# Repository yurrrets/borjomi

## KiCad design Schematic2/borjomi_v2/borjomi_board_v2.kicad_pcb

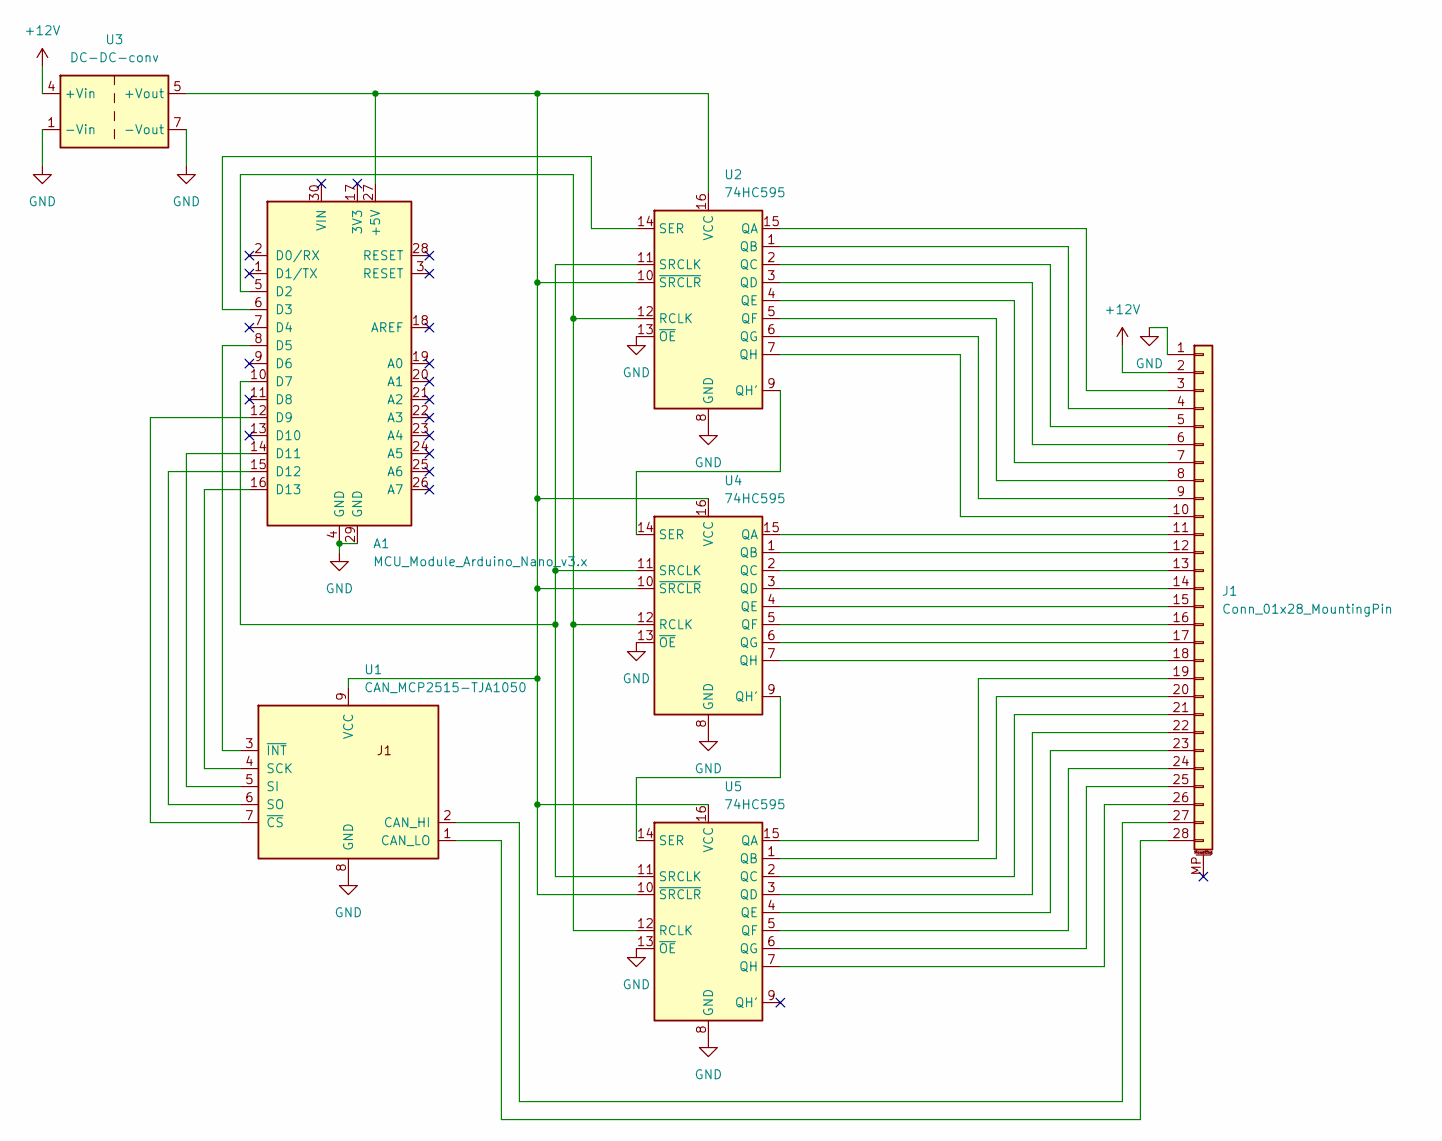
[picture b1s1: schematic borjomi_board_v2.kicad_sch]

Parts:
A1: MCU_Module_Arduino_Nano_v3.x; Arduino_Nano_Holes0.9
J1: Conn_01x28_MountingPin; PinHeader_1x28_P2.54mm_Vertical
U1: CAN_MCP2515-TJA1050; AOC346_MCP2515_Holes0.9
U2, U4, U5: 74HC595; DIP-16_W7.62mm
U3: DC-DC-conv; DC_DC_Step_Out

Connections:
+12V: J1.2, U3.4 (+Vin)
GND: A1.4 (GND), A1.29 (GND), J1.1, U1.8 (GND), U2.8 (GND), U2.13 (~OE), U3.1 (-Vin), U3.7 (-Vout), U4.8 (GND), U4.13 (~OE), U5.8 (GND), U5.13 (~OE)
unnamed: A1.27 (+5V), U1.9 (VCC), U2.10 (~SRCLR), U2.16 (VCC), U3.5 (+Vout), U4.10 (~SRCLR), U4.16 (VCC), U5.10 (~SRCLR), U5.16 (VCC)
unnamed: A1.5 (D2), U2.12 (RCLK), U4.12 (RCLK), U5.12 (RCLK)
unnamed: A1.6 (D3), U2.14 (SER)
unnamed: A1.8 (D5), U1.3 (~INT)
unnamed: A1.10 (D7), U2.11 (SRCLK), U4.11 (SRCLK), U5.11 (SRCLK)
unnamed: A1.12 (D9), U1.7 (~CS)
unnamed: A1.14 (D11), U1.5 (SI)
unnamed: A1.15 (D12), U1.6 (SO)
unnamed: A1.16 (D13), U1.4 (SCK)
unnamed: J1.3, U2.15 (QA)
unnamed: J1.4, U2.1 (QB)
unnamed: J1.5, U2.2 (QC)
unnamed: J1.6, U2.3 (QD)
unnamed: J1.7, U2.4 (QE)
unnamed: J1.8, U2.5 (QF)
unnamed: J1.9, U2.6 (QG)
unnamed: J1.10, U2.7 (QH)
unnamed: J1.11, U4.15 (QA)
unnamed: J1.12, U4.1 (QB)
unnamed: J1.13, U4.2 (QC)
unnamed: J1.14, U4.3 (QD)
unnamed: J1.15, U4.4 (QE)
unnamed: J1.16, U4.5 (QF)
unnamed: J1.17, U4.6 (QG)
unnamed: J1.18, U4.7 (QH)
unnamed: J1.19, U5.15 (QA)
unnamed: J1.20, U5.1 (QB)
unnamed: J1.21, U5.2 (QC)
unnamed: J1.22, U5.3 (QD)
unnamed: J1.23, U5.4 (QE)
unnamed: J1.24, U5.5 (QF)
unnamed: J1.25, U5.6 (QG)
unnamed: J1.26, U5.7 (QH)
unnamed: J1.27, U1.2 (CAN_HI)
unnamed: J1.28, U1.1 (CAN_LO)
unnamed: U2.9 (QH'), U4.14 (SER)
unnamed: U4.9 (QH'), U5.14 (SER)

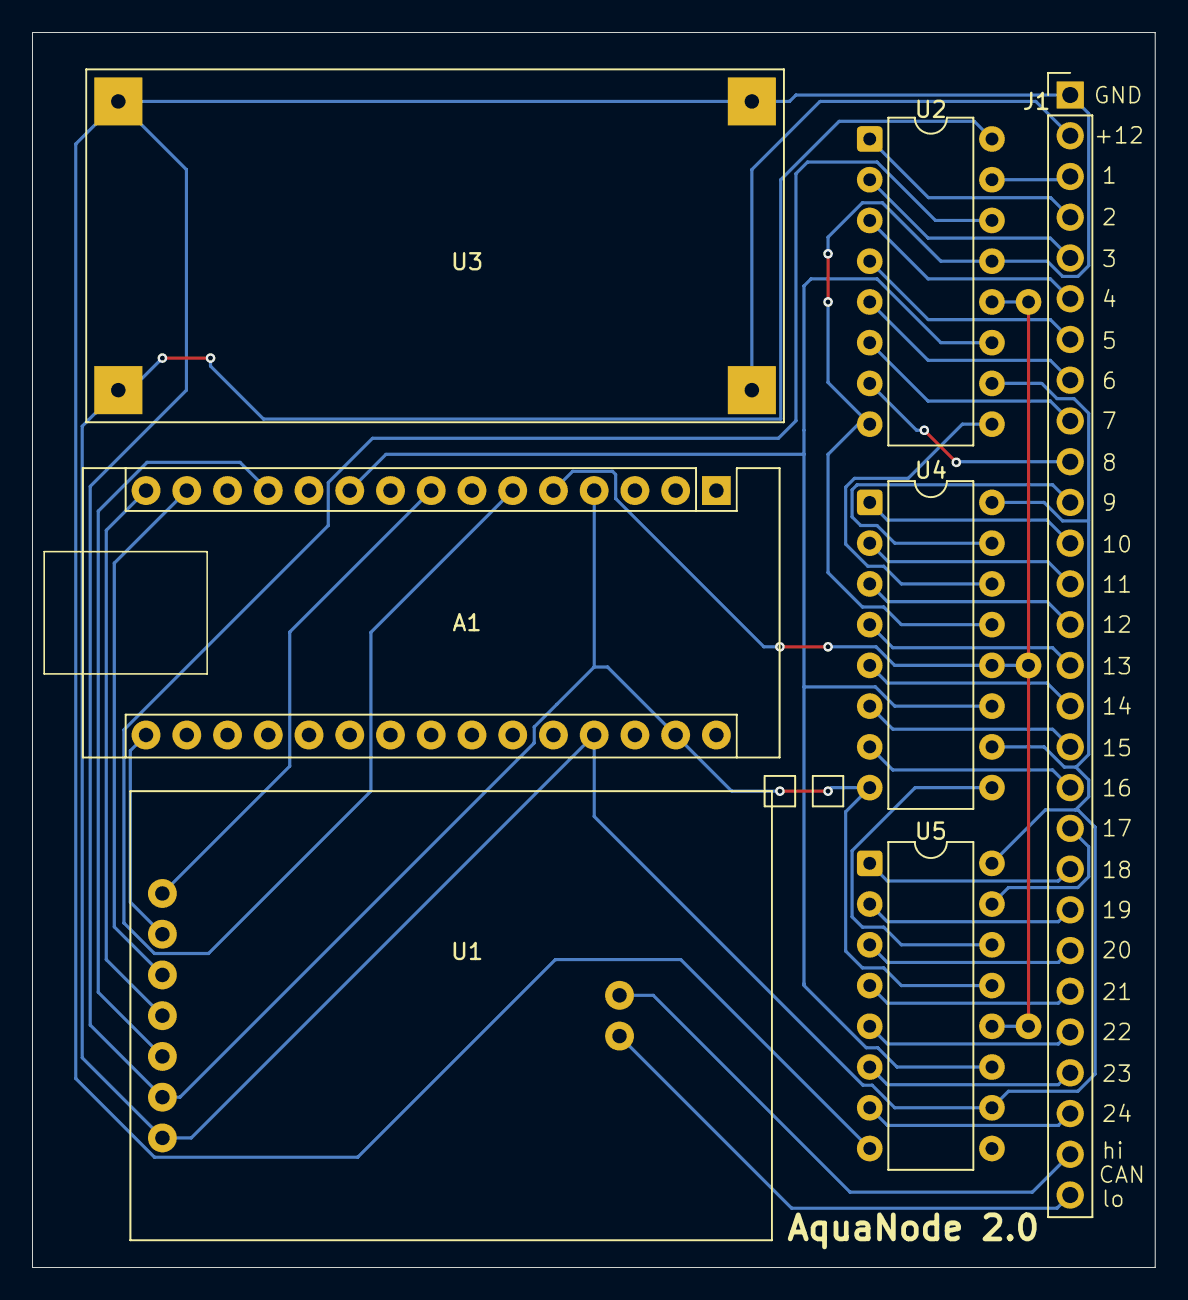
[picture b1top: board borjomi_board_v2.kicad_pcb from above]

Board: 2 copper layers, 70.0 x 77.0 mm, 7 parts (0 on the bottom side), 39 nets.

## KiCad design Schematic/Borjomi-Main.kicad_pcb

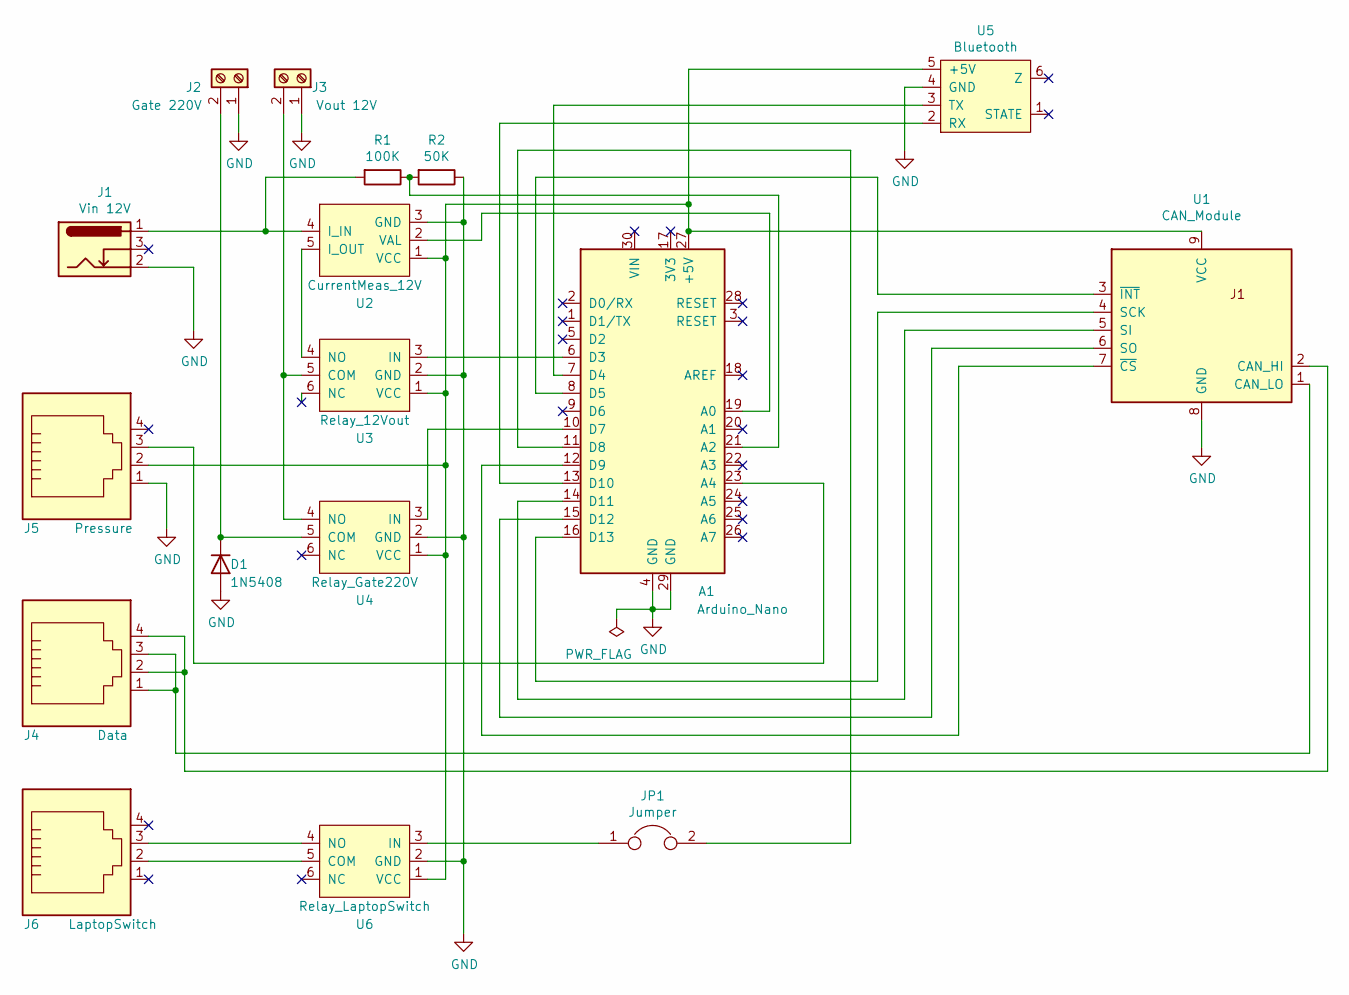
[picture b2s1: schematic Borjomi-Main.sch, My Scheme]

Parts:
A1: Arduino_Nano; Arduino_Nano_Holes0.9
D1: 1N5408; D_DO-27_P5.08mm_Vertical_KathodeUp
J1: Vin 12V; BarrelJack_Horizontal
J2: Gate 220V; Degson_DG301_1x02_P5.00mm_Horizontal
J3: Vout 12V; Degson_DG301_1x02_P5.00mm_Horizontal
J4: Data; RJ14_YH-57-21_5722_6P4C
J5: Pressure; RJ14_YH-57-21_5722_6P4C
J6: LaptopSwitch; RJ14_YH-57-21_5722_6P4C
JP1: Jumper; SimpleJumper_Pitch5.08mm_Drill0.7mm_2pad
R1: 100K; R_Box_L8.4mm_W2.5mm_P5.08mm
R2: 50K; R_Box_L8.4mm_W2.5mm_P5.08mm
U1: CAN_Module; AOC346_MCP2515_Holes0.9
U2: CurrentMeas_12V; ACS712
U3: Relay_12Vout; Relay_Module_1_Channel_Holes0.9
U4: Relay_Gate220V; Relay_Module_1_Channel_Holes0.9
U5: Bluetooth; HC-05
U6: Relay_LaptopSwitch; Relay_Module_1_Channel_Holes0.9

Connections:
GND: A1.4 (GND), A1.29 (GND), D1.2 (A), J1.2, J2.1, J3.1, J5.1, R2.1, U1.8 (GND), U2.3 (GND), U3.2 (GND), U4.2 (GND), U5.4 (GND), U6.2 (GND)
unnamed: A1.6 (D3), U3.3 (IN)
unnamed: A1.7 (D4), U5.3 (TX)
unnamed: A1.8 (D5), U1.3 (~INT)
unnamed: A1.10 (D7), U4.3 (IN)
unnamed: A1.11 (D8), JP1.2
unnamed: A1.12 (D9), U1.7 (~CS)
unnamed: A1.13 (D10), U5.2 (RX)
unnamed: A1.14 (D11), U1.5 (SI)
unnamed: A1.15 (D12), U1.6 (SO)
unnamed: A1.16 (D13), U1.4 (SCK)
unnamed: A1.19 (A0), U2.2 (VAL)
unnamed: A1.21 (A2), R1.1, R2.2
unnamed: A1.23 (A4), J5.3
unnamed: A1.27 (+5V), J5.2, U1.9 (VCC), U2.1 (VCC), U3.1 (VCC), U4.1 (VCC), U5.5 (+5V), U6.1 (VCC)
unnamed: D1.1 (K), J2.2, U4.5 (COM)
unnamed: J1.1, R1.2, U2.4 (I_IN)
unnamed: J3.2, U3.5 (COM), U4.4 (NO)
unnamed: J4.1, J4.3, U1.1 (CAN_LO)
unnamed: J4.2, J4.4, U1.2 (CAN_HI)
unnamed: J6.2, U6.5 (COM)
unnamed: J6.3, U6.4 (NO)
unnamed: JP1.1, U6.3 (IN)
unnamed: U2.5 (I_OUT), U3.4 (NO)

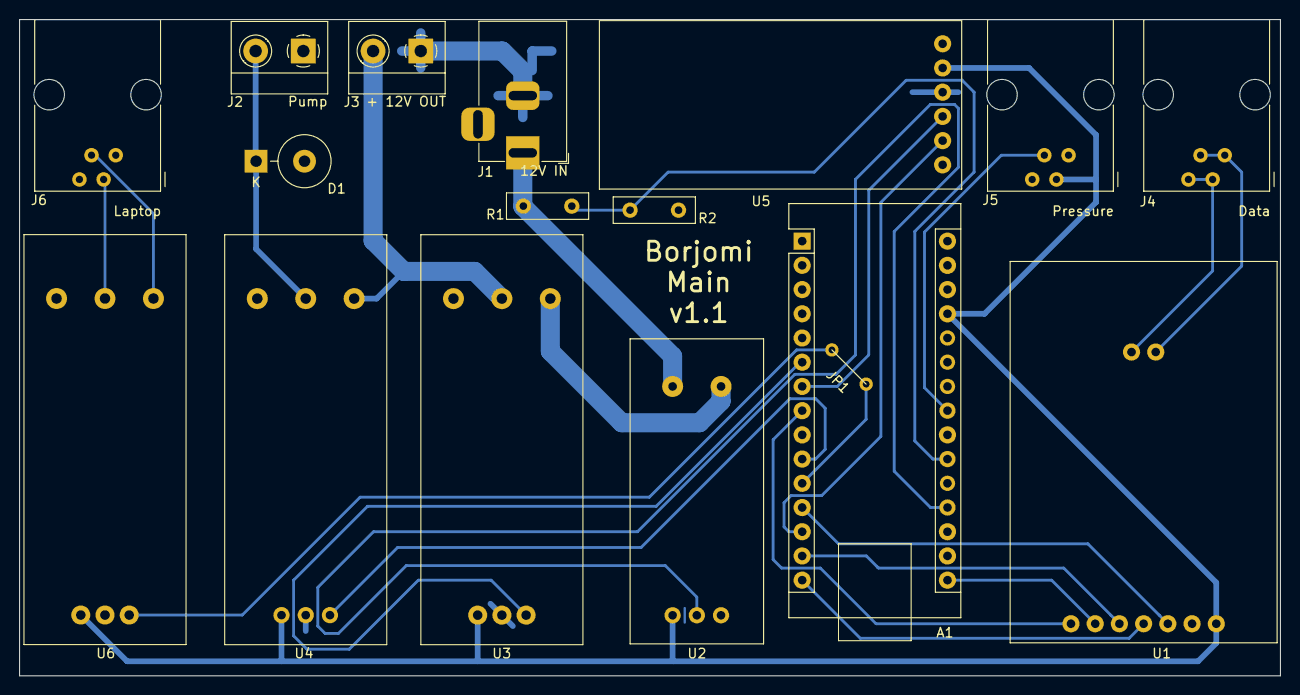
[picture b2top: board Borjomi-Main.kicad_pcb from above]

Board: 2 copper layers, 132.3 x 68.8 mm, 17 parts (0 on the bottom side), 24 nets.

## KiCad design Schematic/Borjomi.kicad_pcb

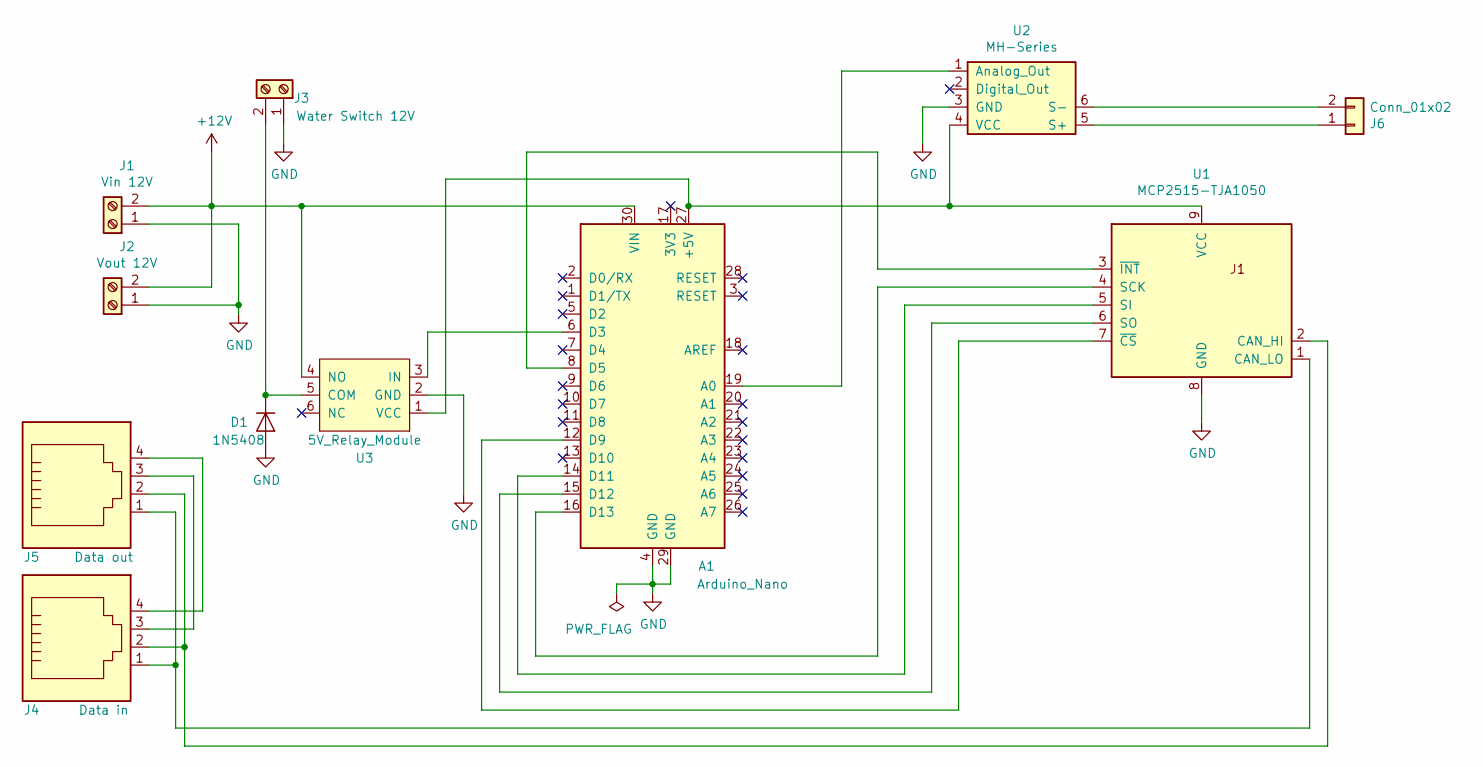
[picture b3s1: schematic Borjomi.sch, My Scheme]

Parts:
A1: Arduino_Nano; Arduino_Nano_Holes0.9
D1: 1N5408; D_DO-27_P5.08mm_Vertical_KathodeUp
J1: Vin 12V; Degson_DG301_1x02_P5.00mm_Horizontal
J2: Vout 12V; Degson_DG301_1x02_P5.00mm_Horizontal
J3: Water Switch 12V; Degson_DG301_1x02_P5.00mm_Horizontal
J4: Data in; RJ14_YH-57-21_5722_6P4C
J5: Data out; RJ14_YH-57-21_5722_6P4C
J6: Conn_01x02; Degson_DG301_1x02_P5.00mm_Horizontal
U1: MCP2515-TJA1050; AOC346_MCP2515_Holes0.9
U2: MH-Series; MH_Sensor_Holes0.9
U3: 5V_Relay_Module; Relay_Module_1_Channel_Holes0.9

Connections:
+12V: A1.30 (VIN), J1.2, J2.2, U3.4 (NO)
GND: A1.4 (GND), A1.29 (GND), D1.2 (A), J1.1, J2.1, J3.1, U1.8 (GND), U2.3 (GND), U3.2 (GND)
unnamed: A1.6 (D3), U3.3 (IN)
unnamed: A1.8 (D5), U1.3 (~INT)
unnamed: A1.12 (D9), U1.7 (~CS)
unnamed: A1.14 (D11), U1.5 (SI)
unnamed: A1.15 (D12), U1.6 (SO)
unnamed: A1.16 (D13), U1.4 (SCK)
unnamed: A1.19 (A0), U2.1 (Analog_Out)
unnamed: A1.27 (+5V), U1.9 (VCC), U2.4 (VCC), U3.1 (VCC)
unnamed: D1.1 (K), J3.2, U3.5 (COM)
unnamed: J4.1, J5.1, U1.1 (CAN_LO)
unnamed: J4.2, J5.2, U1.2 (CAN_HI)
unnamed: J4.3, J5.3
unnamed: J4.4, J5.4
unnamed: J6.1, U2.5 (S+)
unnamed: J6.2, U2.6 (S-)

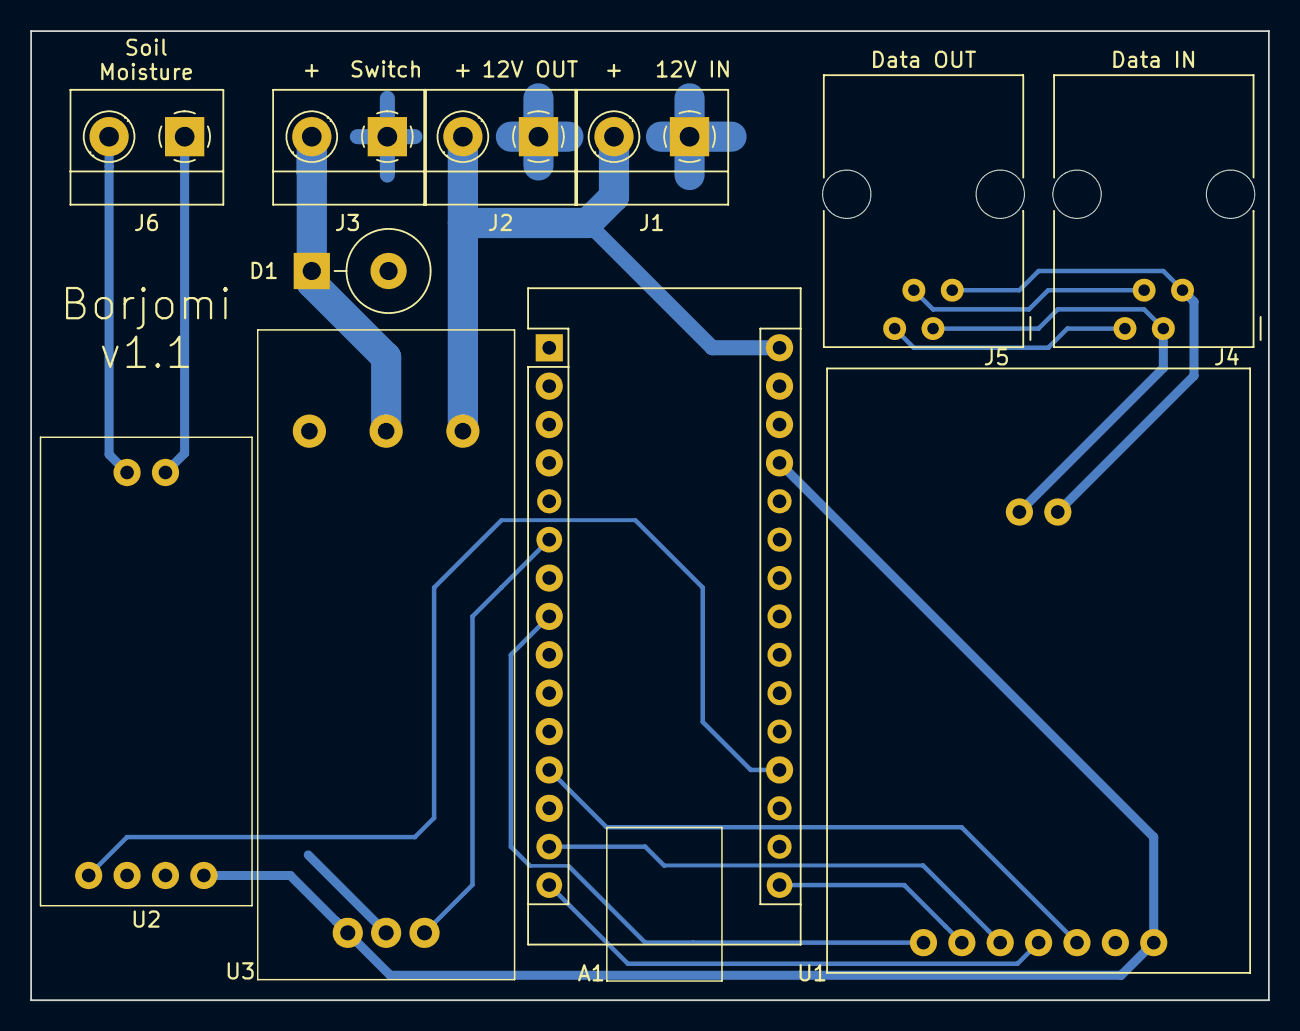
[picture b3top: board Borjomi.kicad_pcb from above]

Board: 2 copper layers, 81.9 x 64.1 mm, 11 parts (0 on the bottom side), 17 nets.

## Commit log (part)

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2018-09-18 add Arduino folder
2018-09-24 Add Creator files for common node
2018-09-27 Add Bluetooth protocol (draft), and first code to work with BT
2018-09-28 Add bluetooth support for water on/off command
2018-09-29 Reorganize code in master node
    Also recompile slave nodes for new EEPROM library
2018-09-29 Implement CMD_GET_WATER_SWITCH, plus code reorganization
2018-09-29 Improve CMD_GET_WATER_SWITCH answer
2018-09-30 Implement protocol on slave node side. Plus
    implement ANALOG_READ on higher level
2018-10-13 Add capabilities defines. BT protocol v0.2 description.
2018-11-01 Some updates
2018-11-01 Protocol implementation for slave node, modify existing BT commands
2018-11-03 Add version script
2018-11-03 Fixes to last commit
2018-11-03 Turn off debug prints, soil moisture value inversing
2018-11-25 Add doc folder; add electric scheme near water pump
2019-04-04 Add relay module (scheme, lib, footprint)
2019-04-05 Add footprints for components; add pcb basic
2019-04-08 Pcb v1.0 + gerber files
2019-04-21 PCB v1.1 + gerber
2019-06-13 Add "borjomi-main" board
    1) Scematics (full)
    2) PCB layout (partly done)
2019-06-13 Borjomi-main: almost final pcb
2019-06-14 Fix few bugs
2019-06-14 Generate gerber files
2019-06-18 Update schematics/pcb to use barrel_connector as 12V IN
2019-08-04 v1.1. Fix bug with voltage divider
    Also update gerber/drill files
2019-08-04 Update code to hardware
2019-08-07 Extend cmd_codes.h with master-node commands
    Also partially implemented handler in master-node
    slave-node: actualize to hw
2019-08-08 Fix build and assign correct pin numbers (in master node)
2019-08-08 Add master-node-cfg project
2019-08-08 Update pcb for Borjomi-main
2019-08-08 Add full support of commands for master node
    Also bugfix and mini refactoring
2019-09-17 Add serial device; add functionality for buttons
2019-09-17 SimpleControl C++: listen to open serial port; improve UI
2020-01-07 Add borjomi-server (first rev)
2020-01-08 Add mysql db create script
2020-01-08 Add first functionality for accounts page
2020-01-08 Create settings for project start/debug (for vscode)
2020-01-20 Add borjomi-server2 (web socket)
2020-01-24 create basic directory structure
2020-01-24 Add more infrastucture objects
2020-01-27 borjomi-server2: add login stub function
2020-01-31 add tests
2020-02-02 Make login.login function works [simple impl]
2020-02-04 Fix tests, add init/finish to DB module
2020-02-04 Add ensureLogin() function and unit test for it
2020-02-06 add getChildAccounts/hasChildAccount functions and tests for them
2020-02-10 add Message concept (type declaration only)
2020-02-11 Add functions db.createMessage/db.removeMessage and unit test for them
2020-02-11 Rename table account_tokens -> account_token
2020-02-13 Remove unnecessary status from Message. Implement h_message.newMessage function
2020-02-13 Start code for broker
2020-02-14 Improve Broker. Add test for it
2020-02-15 Fix sql dump to work on Ubuntu
2020-02-16 Message processing from server side (mid-work)
2020-02-18 Add "ping" message processing on server; add funcs to wsServer
2020-02-20 Fix bugs in broker and other places, implement message mechanism
    Also update html test form
2020-02-24 Implement send message to client
2020-02-27 Add h_message.updateMessageStatus function
2020-02-29 Add functions: updateMessageStatus, setMessageAnswer
    Also implement "ping" message reaction on html client
2020-02-29 Inform sequesters about message status change / answered
2020-03-02 Send message on client connect Also rename messageAnswer.notes => result; other improvements
2020-03-22 Message processing func on server side now returns msg.id+MessageAnswer
    Instead of setting MessageAnswer by theirself
2020-03-22 Message processing by Server for the ones that comes from Client module
2020-03-22 Add separate function "answerMessage" in Client module
2020-03-22 Add PeriodicPing of Server from Client module
2020-03-30 Add basic functions to work with Arduino module
2020-04-09 Implement Arduino's ping and version functions
2020-04-09 Update bt_protocol - fix error in descr
2020-04-11 Fix bugs in h_arduino and corresponding unit test
2020-04-18 Server: Queue added while work with Arduino SerialPort
2020-04-18 WaterSchemePage added (browser client); very first rev, base functional
2020-04-30 Add sendMsgLikeWsCallFunction on html client
2020-04-30 Server as Client: allow to call function if message not found
    If message type is not registered, but function with the same registered, call the function like it's message
2020-05-01 Remove unused files
2020-05-01 Publish in WS some login functions
    Also change their interface to satisfy ws function requirements, and fix broken tests,
2020-05-01 Fix server's client behaviour when processing message as server function
2020-05-01 Fix message answer (return result as object, not as string)
2020-05-01 More logging for called ws functions/messages
2020-05-02 Handle errors that may come with function call result from server
2020-05-02 Ignore some C++ files
2020-05-02 Add package "serialport" to server projects
2020-05-02 Implement all arduino functions on server side
    Also calls on client, and small bugfixes
2020-05-06 WebSocket service was changed to rxjs pattern
2020-05-11 Add auto start PC functionality
2020-06-27 Rename "login.js" to "h_login.js"
    Also fix unit test
2020-06-27 Make sample-configs and ignore real local configs
2020-06-27 Update package.json and package-lock.json
    Also remove outdated MantaTest.html
2020-06-27 Add static hosting of html page
2020-07-19 Bump lodash from 4.17.15 to 4.17.19 in /Server/borjomi-server
    Bumps [lodash](https://github.com/lodash/lodash) from 4.17.15 to 4.17.19.
    - [Release notes](https://github.com/lodash/lodash/releases)
    - [Commits](https://github.com/lodash/lodash/compare/4.17.15...4.17.19)
2020-08-30 Board Borjomi-Main v1.1 with Gerber/Drill files
2020-09-04 Bump node-sass from 4.13.0 to 4.14.1 in /Server/borjomi-server
    Bumps [node-sass](https://github.com/sass/node-sass) from 4.13.0 to 4.14.1.
    - [Release notes](https://github.com/sass/node-sass/releases)
    - [Changelog](https://github.com/sass/node-sass/blob/master/CHANGELOG.md)
    - [Commits](https://github.com/sass/node-sass/compare/v4.13.0...v4.14.1)
2020-10-09 Change IO channel for MasterNode from BT to ttyUSB
2021-05-10 Bump lodash from 4.17.19 to 4.17.21 in /Server/borjomi-server
    Bumps [lodash](https://github.com/lodash/lodash) from 4.17.19 to 4.17.21.
    - [Release notes](https://github.com/lodash/lodash/releases)
    - [Commits](https://github.com/lodash/lodash/compare/4.17.19...4.17.21)
2021-05-11 Bump hosted-git-info from 2.8.5 to 2.8.9 in /Server/borjomi-server
    Bumps [hosted-git-info](https://github.com/npm/hosted-git-info) from 2.8.5 to 2.8.9.
    - [Release notes](https://github.com/npm/hosted-git-info/releases)
    - [Changelog](https://github.com/npm/hosted-git-info/blob/v2.8.9/CHANGELOG.md)
    - [Commits](https://github.com/npm/hosted-git-info/compare/v2.8.5...v2.8.9)
2021-07-03 Update master-node functionality
    Turn off PcStart module, add check for DcAdapter voltage
2021-07-03 Update Server to new HW config
    Connection using Arduino rs232 chip
2021-07-03 Extend client node list (up to node 180)
2021-07-21 Update WaterScheme with current node config
2021-07-21 Fix errors after prev commit
2021-08-11 Bump path-parse from 1.0.6 to 1.0.7 in /Server/borjomi-server
    Bumps [path-parse](https://github.com/jbgutierrez/path-parse) from 1.0.6 to 1.0.7.
    - [Release notes](https://github.com/jbgutierrez/path-parse/releases)
    - [Commits](https://github.com/jbgutierrez/path-parse/commits/v1.0.7)
    ---
    updated-dependencies:
    - dependency-name: path-parse
2021-09-02 Split arduino funcs and service handlers
2021-09-05 Add all nodes to html page
2021-09-15 Change messages a little
2021-09-15 Actualize real nodes config
2021-09-15 Change active port to USB0 (instead of USB1)
2021-09-15 Change range for DC voltage. For now master node can't detect voltage enough precise
2022-02-11 Bump karma from 4.4.1 to 6.3.14 in /ClientApp/borjomi-client-app
    Bumps [karma](https://github.com/karma-runner/karma) from 4.4.1 to 6.3.14.
    - [Release notes](https://github.com/karma-runner/karma/releases)
    - [Changelog](https://github.com/karma-runner/karma/blob/master/CHANGELOG.md)
    - [Commits](https://github.com/karma-runner/karma/compare/v4.4.1...v6.3.14)
    ---
    updated-dependencies:
2022-02-12 Bump ajv from 6.10.2 to 6.12.6 in /Server/borjomi-server
    Bumps [ajv](https://github.com/ajv-validator/ajv) from 6.10.2 to 6.12.6.
    - [Release notes](https://github.com/ajv-validator/ajv/releases)
    - [Commits](https://github.com/ajv-validator/ajv/compare/v6.10.2...v6.12.6)
    ---
    updated-dependencies:
    - dependency-name: ajv
2022-05-14 fix bug with undefined logger
2022-06-03 Bump @angular/core from 9.1.0 to 11.0.5 in /ClientApp/borjomi-client-app
    Bumps [@angular/core](https://github.com/angular/angular/tree/HEAD/packages/core) from 9.1.0 to 11.0.5.
    - [Release notes](https://github.com/angular/angular/releases)
    - [Changelog](https://github.com/angular/angular/blob/main/CHANGELOG.md)
    - [Commits](https://github.com/angular/angular/commits/11.0.5/packages/core)
    ---
    updated-dependencies:
2022-12-10 Bump express from 4.16.4 to 4.17.3 in /Server/borjomi-server
    Bumps [express](https://github.com/expressjs/express) from 4.16.4 to 4.17.3.
    - [Release notes](https://github.com/expressjs/express/releases)
    - [Changelog](https://github.com/expressjs/express/blob/master/History.md)
    - [Commits](https://github.com/expressjs/express/compare/4.16.4...4.17.3)
    ---
    updated-dependencies:
2023-03-03 Bump minimist and mkdirp in /Server/borjomi-server
    Bumps [minimist](https://github.com/minimistjs/minimist) and [mkdirp](https://github.com/isaacs/node-mkdirp). These dependencies needed to be updated together.
    Updates `minimist` from 1.2.0 to 1.2.8
    - [Release notes](https://github.com/minimistjs/minimist/releases)
    - [Changelog](https://github.com/minimistjs/minimist/blob/main/CHANGELOG.md)
    - [Commits](https://github.com/minimistjs/minimist/compare/v1.2.0...v1.2.8)
    Updates `mkdirp` from 0.5.1 to 0.5.6
2024-01-02 replace Makefiles with cmake builds; add build.sh script
2024-01-02 fix some compiler warnings
2024-02-04 Move main-loop func to class-loop func
    Make CanCommands stateful, and work with setup-loop scheme. Introduce
    BTCommandProcessor. Use btCommandParser and canCommands as dependencies
    for new class. Move most of code from main-loop func to entity-loop
    func.
2024-02-18 Basic implementation of scenario runner
2024-02-18 More correct command processing in can_commands
    Also apply clang formatting to can_commands, and add clang-format file
2024-02-18 Add basic start/stop scenario by button press
2024-02-18 Use lib-lcd for showing current state
2024-03-03 Fix ScenarioRunner. Add unit tests for ScenarioRunner
    Add infastructure for supporting Arduino simulations. Change master-node
    and common-node sources to be unit testable and easy mockable. Add
    gtest/gmock repo as submodule. Write basic unit tests for Arduino
    Simulations and ScenarioRunner.
2024-03-03 Hide gcc warning "-Wpedantic"
2024-03-08 Add basic logger support. Add build flag with debug
2024-03-08 Add SPI transfer iface to LCD screen
2024-03-08 Implement scenario stop function
2024-03-14 scenario serialize/deserialize functions + test
2024-03-16 Move more string literals to PROG space
2024-03-20 Scenarios run bugs fixed. Add store/read main scenario cmds.
    Added command for storing and reading main scenario. Deserialize now
    parses all until new line character.
    Added reaction on error during sending over CAN bus. Crc8 calcs extended
    to calc up to 65535 bytes data length. To CrcPartial added compile-time
    checks. UpdateCrc and CheckCrc moved to separate functions.
    Tests improved, two more tests added (when error happens on sending over
2024-03-23 Replace bool isRunning with State. Make UI more informative
2025-08-26 Add basic support for few board revisions. Implement SlaveNode rev2 (AquaNode 2.0 board)
2025-08-26 Final FW version for AquaNode 2.0 Plus some small improvements
